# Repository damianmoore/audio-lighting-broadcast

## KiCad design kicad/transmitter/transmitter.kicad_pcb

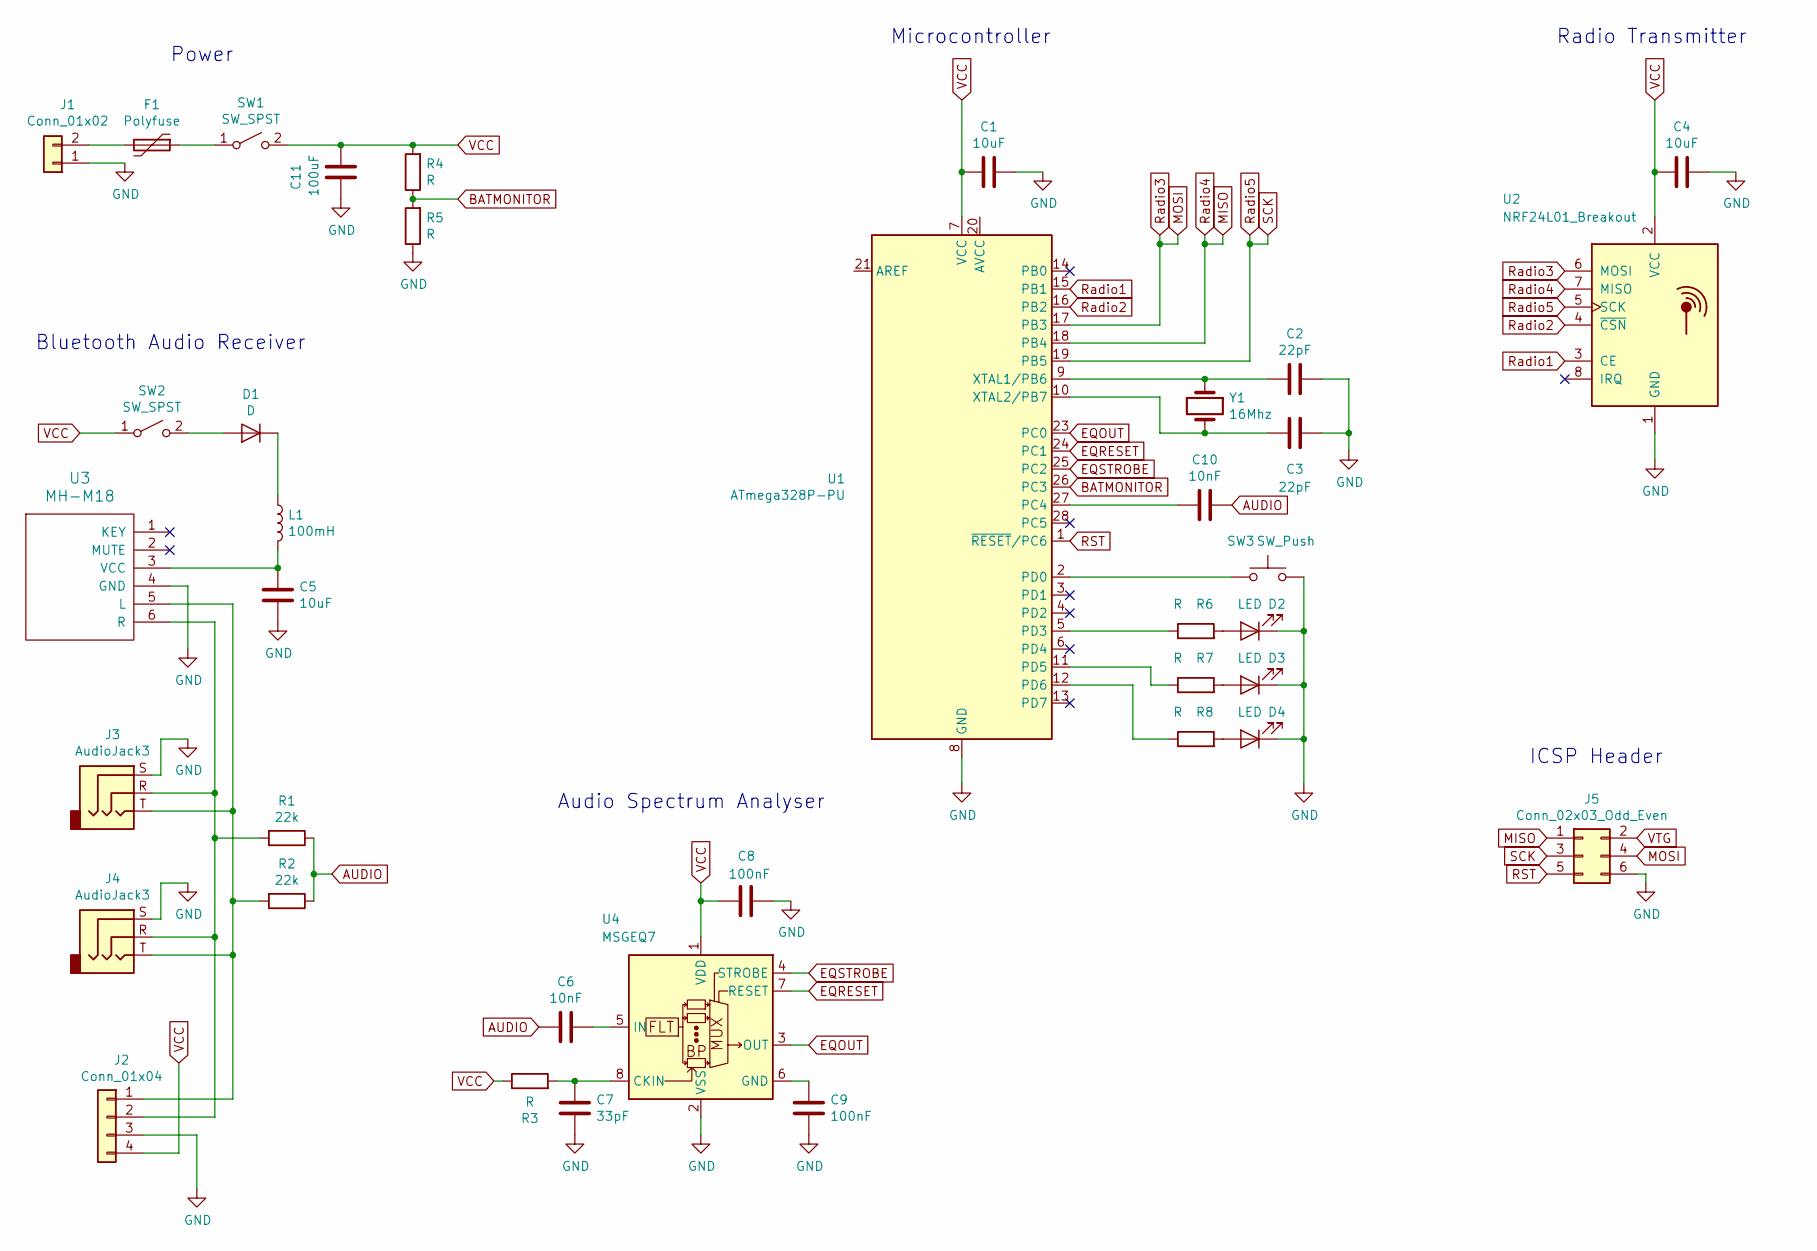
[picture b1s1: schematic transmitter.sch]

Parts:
C1, C4, C5: 10uF; C_0603_1608Metric_Pad1.05x0.95mm_HandSolder
C2, C3: 22pF; C_0603_1608Metric_Pad1.05x0.95mm_HandSolder
C6, C10: 10nF; C_0603_1608Metric_Pad1.05x0.95mm_HandSolder
C7: 33pF; C_0603_1608Metric_Pad1.05x0.95mm_HandSolder
C8, C9: 100nF; C_0603_1608Metric_Pad1.05x0.95mm_HandSolder
C11: 100uF; CP_Radial_D6.3mm_P2.50mm
D1: D; D_A-405_P7.62mm_Horizontal
D2, D3, D4: LED; LED_D3.0mm
F1: Polyfuse; Resonator-2Pin_W6.0mm_H3.0mm
J1: Conn_01x02; SolderWirePad_1x02_P3.81mm_Drill1mm
J2: Conn_01x04; PinHeader_1x04_P2.54mm_Vertical
J3, J4: AudioJack3; 3.5mm_Stereo_Jack
J5: Conn_02x03_Odd_Even; PinHeader_2x03_P2.54mm_Vertical
L1: 100mH; L_Toroid_Vertical_L16.0mm_W8.0mm_P7.62mm
R1, R2: 22k; R_0603_1608Metric_Pad1.05x0.95mm_HandSolder
R3, R4, R5, R6, R7, R8: R; R_0603_1608Metric_Pad1.05x0.95mm_HandSolder
SW1, SW2: SW_SPST; PinHeader_1x02_P2.54mm_Vertical
SW3: SW_Push; PinHeader_1x02_P2.54mm_Vertical
U1: ATmega328P-PU; DIP-28_W7.62mm
U2: NRF24L01_Breakout; nRF24L01_Breakout
U3: MH-M18; MH-M18_Bluetooth_Audio
U4: MSGEQ7; DIP-8_W10.16mm
Y1: 16Mhz; Crystal_HC18-U_Vertical

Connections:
AUDIO: C6.2, C10.1, R1.1, R2.1
BATMONITOR: R4.1, R5.2, U1.26 (PC3)
EQOUT: U1.23 (PC0), U4.3 (OUT)
EQRESET: U1.24 (PC1), U4.7 (RESET)
EQSTROBE: U1.25 (PC2), U4.4 (STROBE)
GND: C1.1, C2.1, C3.1, C4.1, C5.2, C7.1, C8.2, C9.1, C11.1, D2.1 (K), D3.1 (K), D4.1 (K), J1.1, J2.3, J3.S, J4.S, J5.6, R5.1, SW3.2, U1.8 (GND), U1.22 (GND), U2.1 (GND), U3.4 (GND), U4.2 (VSS)
MISO: J5.1, U1.18 (PB4), U2.7 (MISO)
MOSI: J5.4, U1.17 (PB3), U2.6 (MOSI)
unnamed: C2.2, U1.9 (XTAL1/PB6), Y1.1
unnamed: C3.2, U1.10 (XTAL2/PB7), Y1.2
unnamed: C5.1, L1.2, U3.3 (VCC)
unnamed: C6.1, U4.5 (IN)
unnamed: C7.2, R3.2, U4.8 (CKIN)
unnamed: C9.2, U4.6 (GND)
unnamed: C10.2, U1.27 (PC4)
unnamed: D1.1 (K), L1.1
unnamed: D1.2 (A), SW2.2 (B)
unnamed: D2.2 (A), R6.2
unnamed: D3.2 (A), R7.2
unnamed: D4.2 (A), R8.2
unnamed: F1.1, SW1.1 (A)
unnamed: F1.2, J1.2
unnamed: J2.1, J3.T, J4.T, R2.2, U3.5 (L)
unnamed: J2.2, J3.R, J4.R, R1.2, U3.6 (R)
unnamed: R6.1, U1.5 (PD3)
unnamed: R7.1, U1.11 (PD5)
unnamed: R8.1, U1.12 (PD6)
unnamed: SW3.1, U1.2 (PD0)
RST: J5.5, U1.1 (~RESET~/PC6)
Radio1: U1.15 (PB1), U2.3 (CE)
Radio2: U1.16 (PB2), U2.4 (~CSN)
Radio5: J5.3, U1.19 (PB5), U2.5 (SCK)
VCC: C1.2, C4.2, C8.1, C11.2, J2.4, R3.1, R4.2, SW1.2 (B), SW2.1 (A), U1.7 (VCC), U2.2 (VCC), U4.1 (VDD)
VTG: J5.2

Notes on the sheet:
Power
Bluetooth Audio Receiver
Audio Spectrum Analyser
Microcontroller
Radio Transmitter
ICSP Header

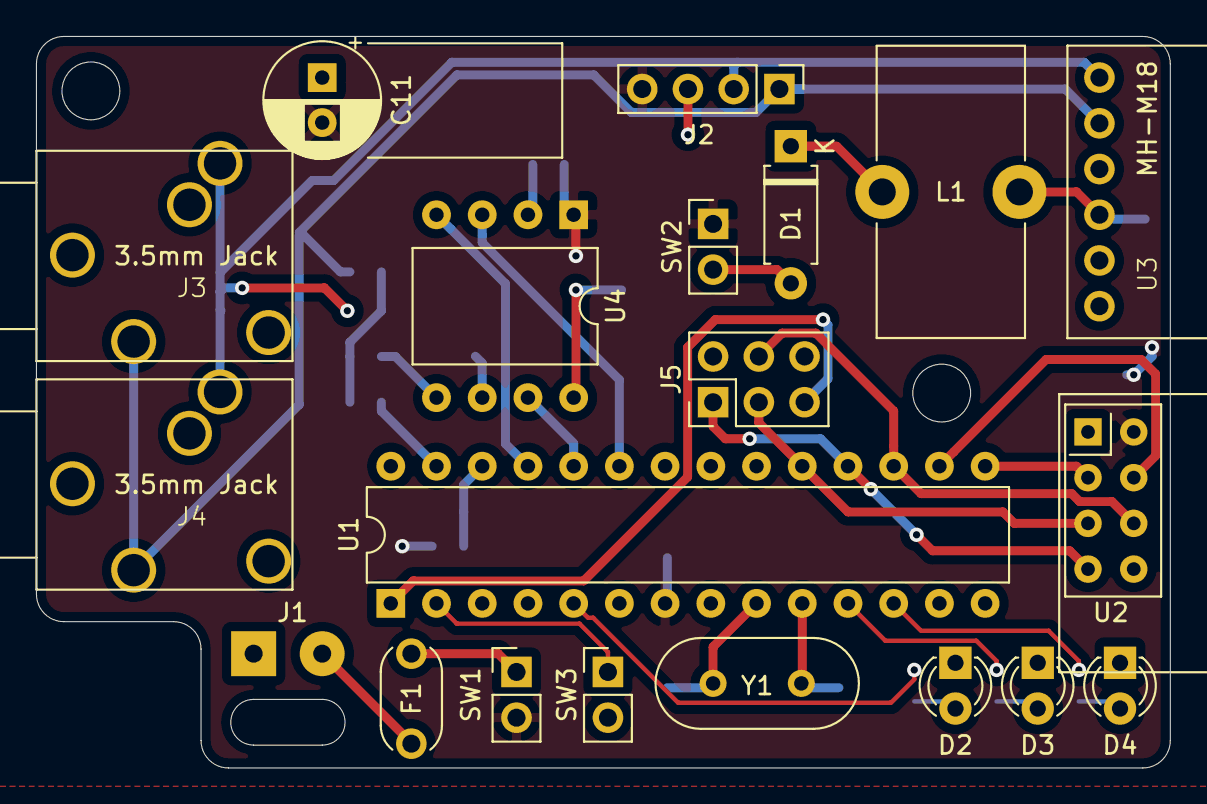
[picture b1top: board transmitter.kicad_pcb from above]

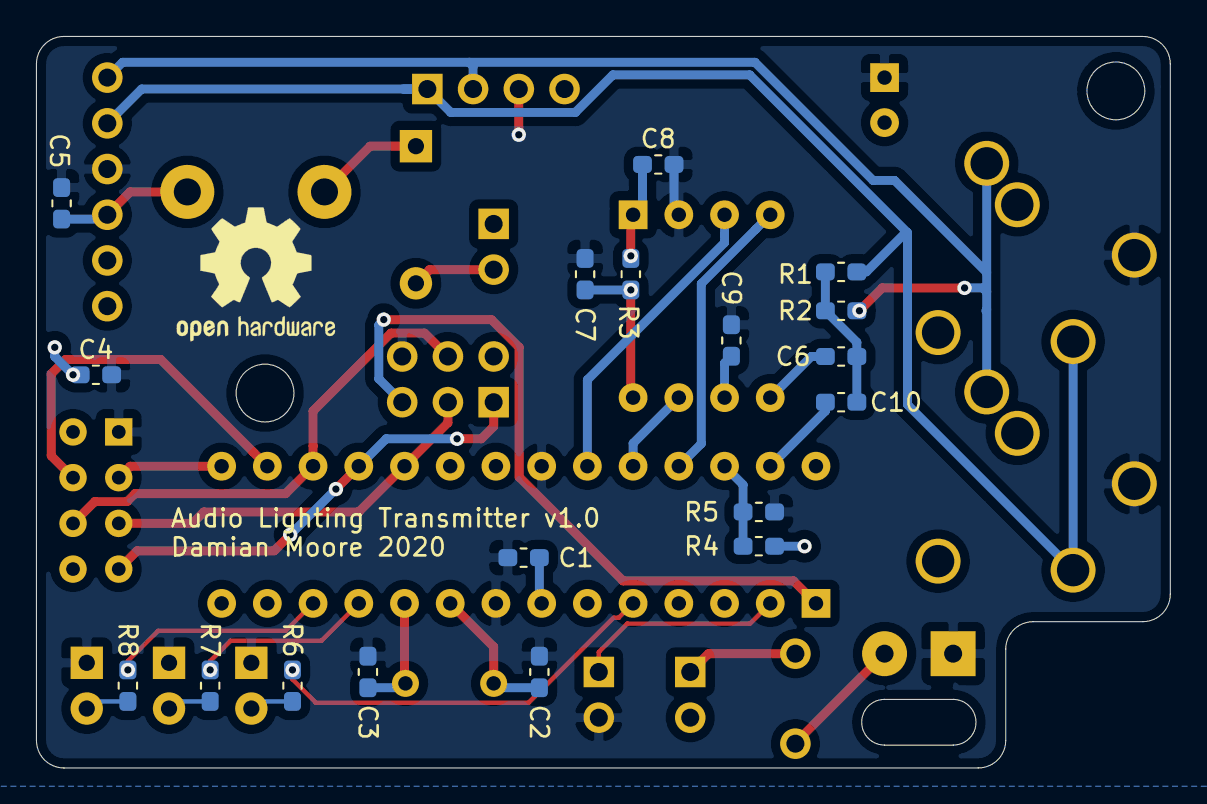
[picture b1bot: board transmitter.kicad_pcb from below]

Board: 2 copper layers, 63.0 x 40.6 mm, 38 parts (18 on the bottom side), 33 nets.

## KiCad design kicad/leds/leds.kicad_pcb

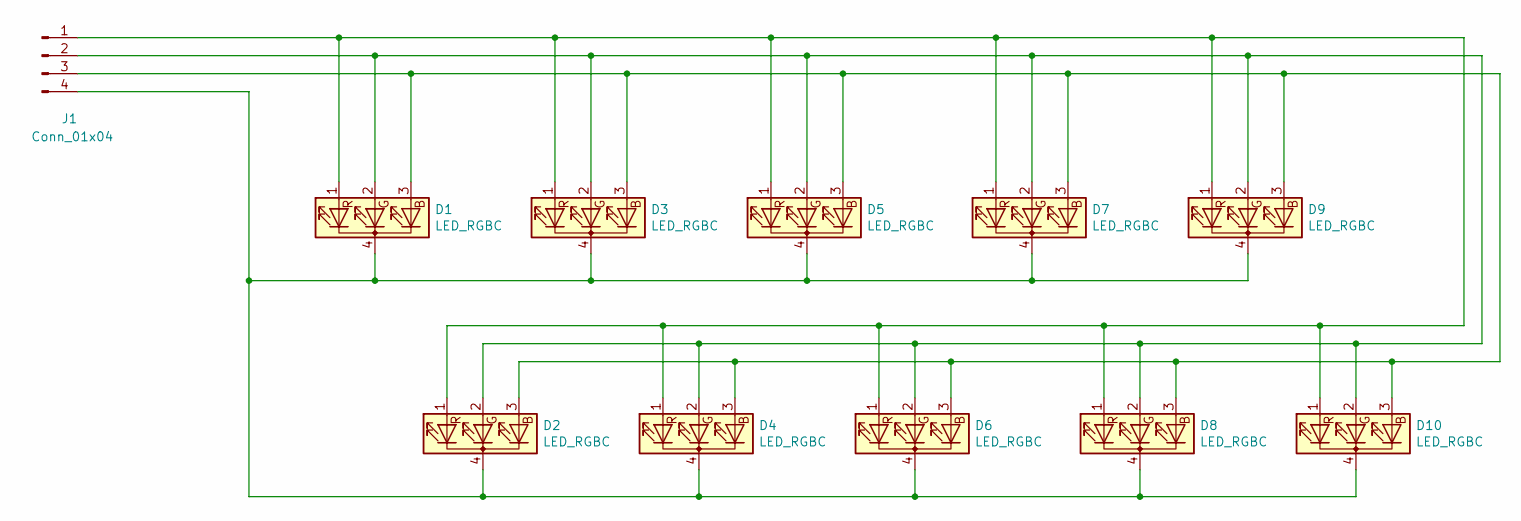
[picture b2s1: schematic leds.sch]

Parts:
D1, D2, D3, D4, D5, D6, D7, D8, D9, D10: LED_RGBC; LED_D5.0mm-4_RGB_swapped_pins
J1: Conn_01x04; Pin_Header_Straight_Simplified_1x04_Pitch2.54mm

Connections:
unnamed: D1.1 (RA), D2.1 (RA), D3.1 (RA), D4.1 (RA), D5.1 (RA), D6.1 (RA), D7.1 (RA), D8.1 (RA), D9.1 (RA), D10.1 (RA), J1.1
unnamed: D1.2 (GA), D2.2 (GA), D3.2 (GA), D4.2 (GA), D5.2 (GA), D6.2 (GA), D7.2 (GA), D8.2 (GA), D9.2 (GA), D10.2 (GA), J1.2
unnamed: D1.3 (BA), D2.3 (BA), D3.3 (BA), D4.3 (BA), D5.3 (BA), D6.3 (BA), D7.3 (BA), D8.3 (BA), D9.3 (BA), D10.3 (BA), J1.3
unnamed: D1.4 (K), D2.4 (K), D3.4 (K), D4.4 (K), D5.4 (K), D6.4 (K), D7.4 (K), D8.4 (K), D9.4 (K), D10.4 (K), J1.4

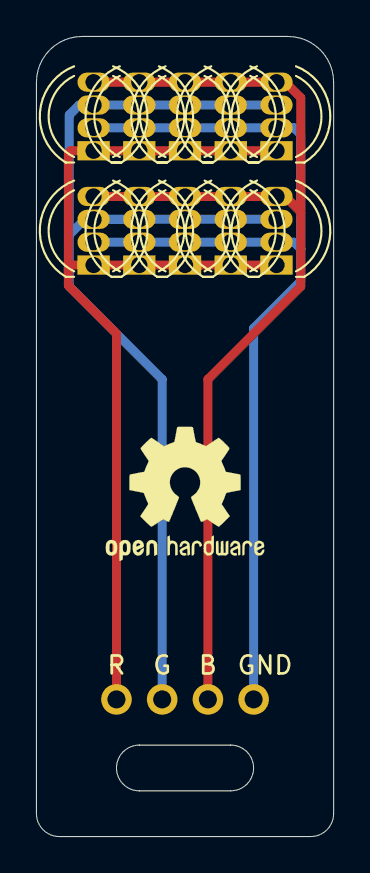
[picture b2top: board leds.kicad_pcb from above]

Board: 2 copper layers, 16.5 x 44.5 mm, 11 parts (0 on the bottom side), 4 nets.

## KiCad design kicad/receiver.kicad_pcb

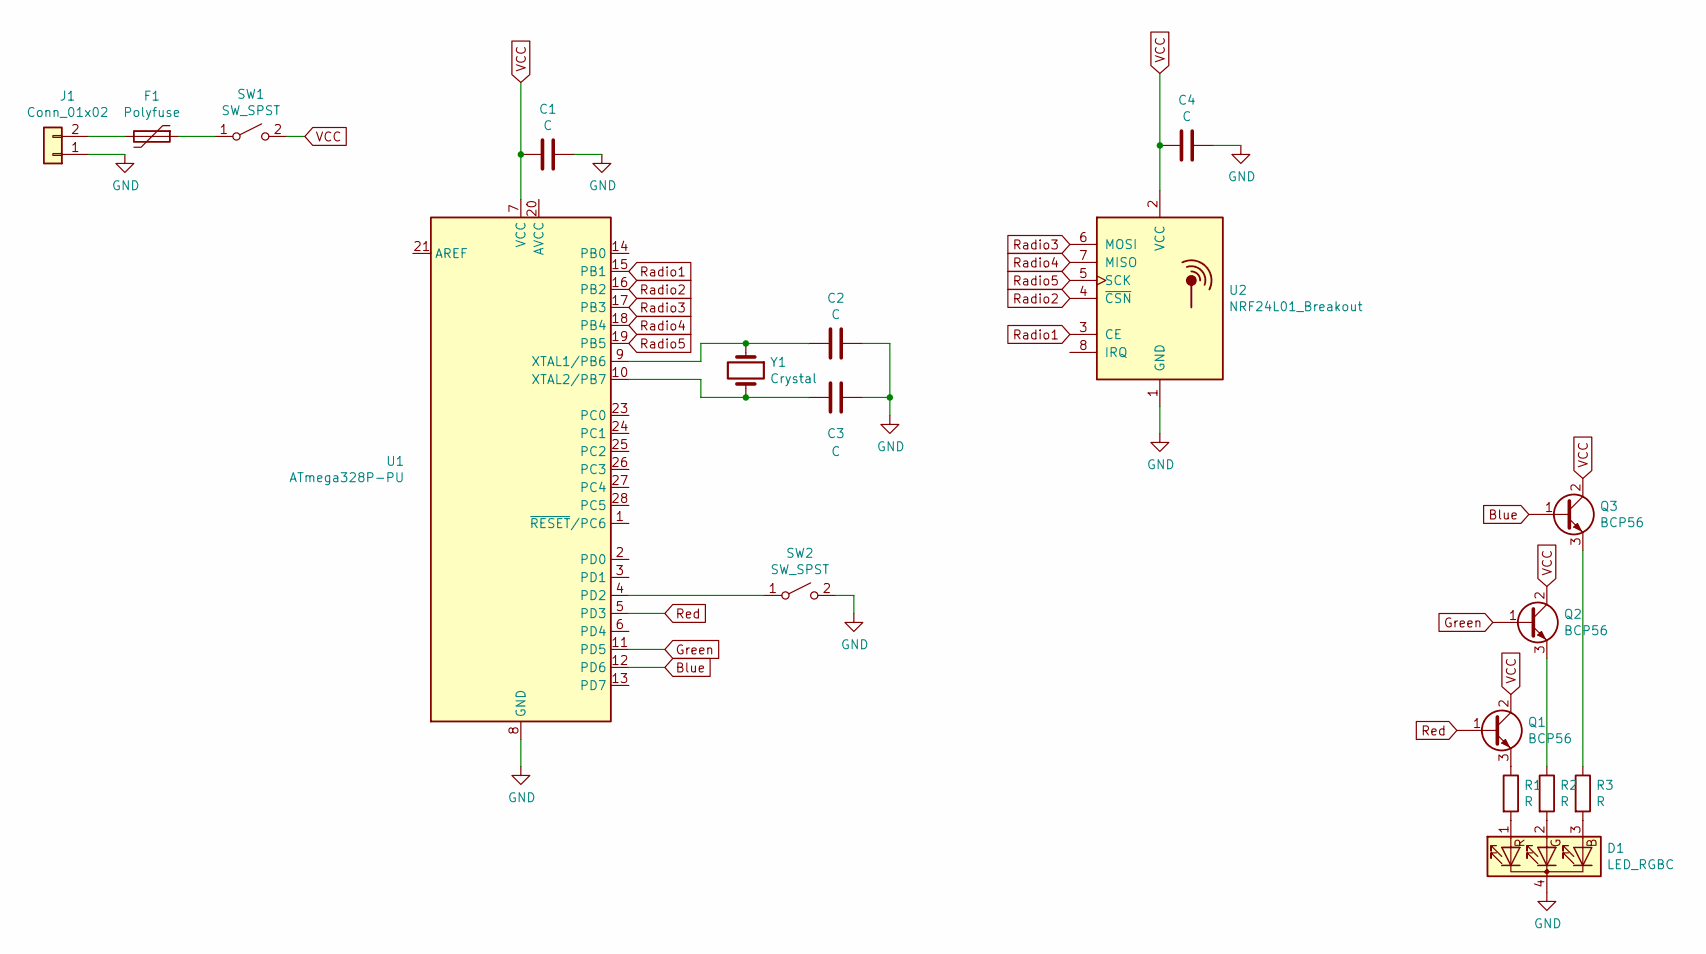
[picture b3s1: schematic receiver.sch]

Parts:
C1, C2, C3, C4: C; C_Disc_D3.0mm_W1.6mm_P2.50mm
D1: LED_RGBC; SolderWirePad_1x04_P3.175mm_Drill0.8mm
F1: Polyfuse; Crystal_HC18-U_Vertical
J1: Conn_01x02; SolderWirePad_1x02_P3.81mm_Drill1mm
Q1, Q2, Q3: BCP56; SOT-223-3_TabPin2
R1, R2, R3: R; R_Axial_DIN0207_L6.3mm_D2.5mm_P7.62mm_Horizontal
SW1, SW2: SW_SPST; SolderWirePad_1x02_P3.81mm_Drill1mm
U1: ATmega328P-PU; DIP-28_W7.62mm
U2: NRF24L01_Breakout; nRF24L01_Breakout
Y1: Crystal; Crystal_HC18-U_Vertical

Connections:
Blue: Q3.1 (B), U1.12 (PD6)
GND: C1.1, C2.1, C3.1, C4.1, D1.4 (K), J1.1, SW2.2 (B), U1.8 (GND), U1.22 (GND), U2.1 (GND)
Green: Q2.1 (B), U1.11 (PD5)
unnamed: C2.2, U1.9 (XTAL1/PB6), Y1.1
unnamed: C3.2, U1.10 (XTAL2/PB7), Y1.2
unnamed: D1.1 (RA), R1.2
unnamed: D1.2 (GA), R2.2
unnamed: D1.3 (BA), R3.2
unnamed: F1.1, SW1.1 (A)
unnamed: F1.2, J1.2
unnamed: Q1.3 (E), R1.1
unnamed: Q2.3 (E), R2.1
unnamed: Q3.3 (E), R3.1
unnamed: SW2.1 (A), U1.4 (PD2)
Radio1: U1.15 (PB1), U2.3 (CE)
Radio2: U1.16 (PB2), U2.4 (~CSN)
Radio3: U1.17 (PB3), U2.6 (MOSI)
Radio4: U1.18 (PB4), U2.7 (MISO)
Radio5: U1.19 (PB5), U2.5 (SCK)
Red: Q1.1 (B), U1.5 (PD3)
VCC: C1.2, C4.2, Q1.2 (C), Q1.4 (C), Q2.2 (C), Q2.4 (C), Q3.2 (C), Q3.4 (C), SW1.2 (B), U1.7 (VCC), U2.2 (VCC)

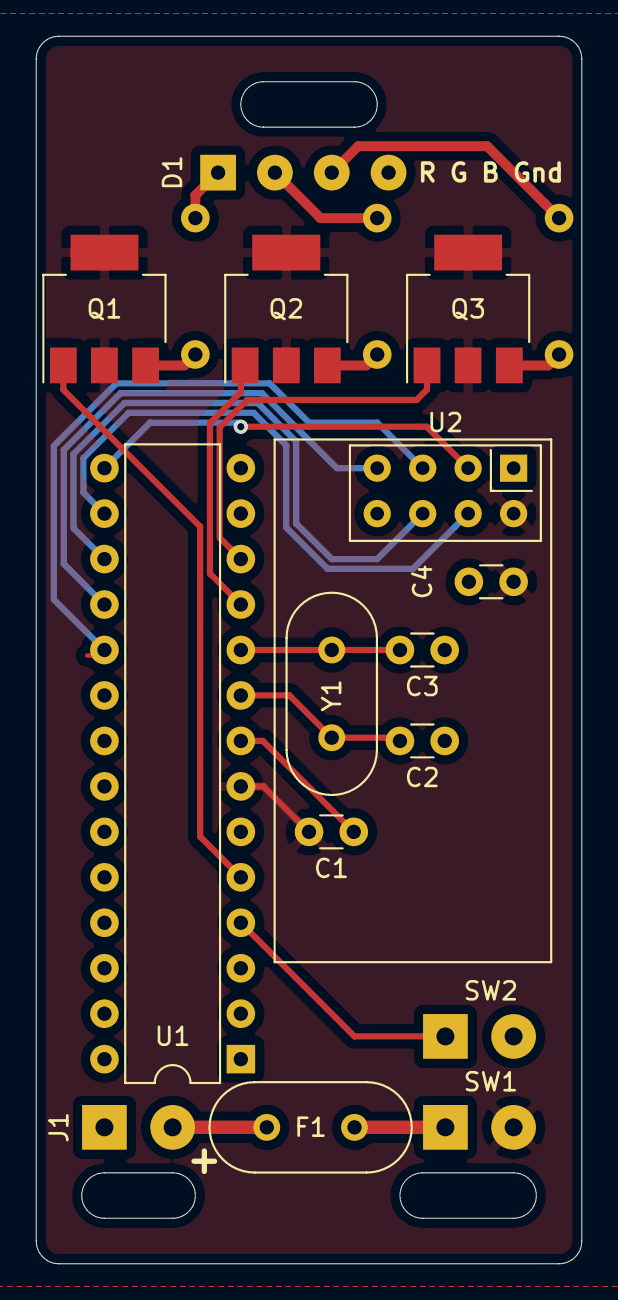
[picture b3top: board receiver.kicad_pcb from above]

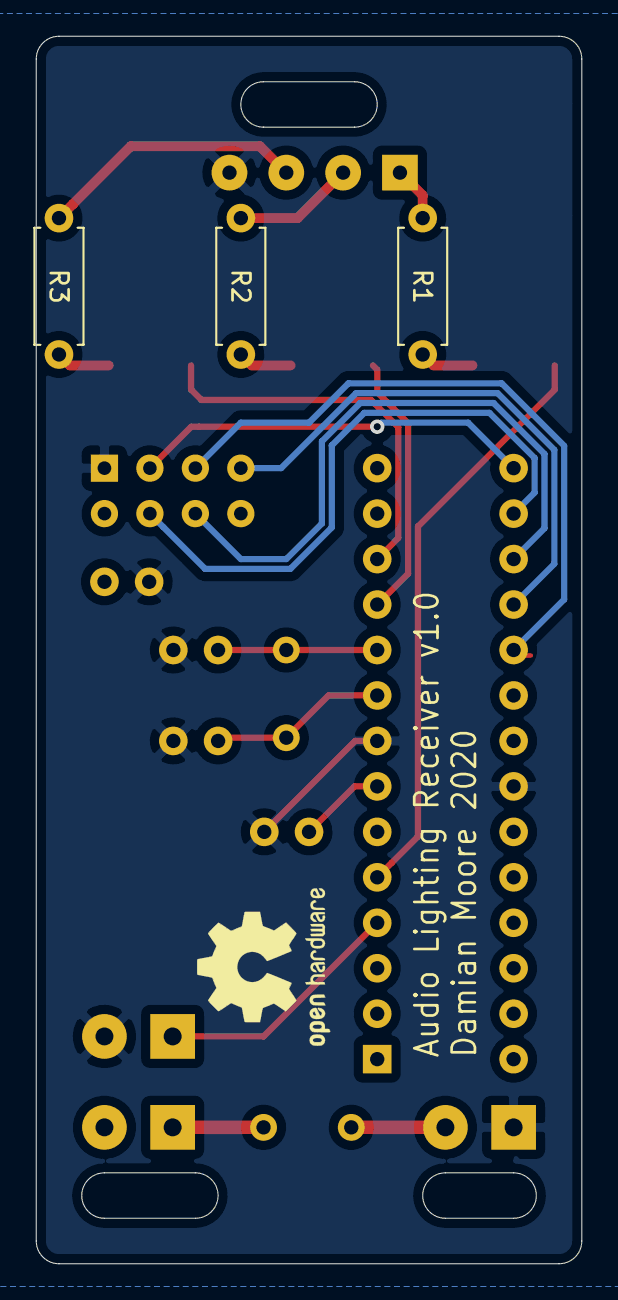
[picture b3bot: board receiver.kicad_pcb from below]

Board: 2 copper layers, 30.5 x 68.6 mm, 18 parts (3 on the bottom side), 21 nets.

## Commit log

2020-01-12 KiCad files for receiver
2020-01-12 Transmitter and receiver Arduino source files
2020-01-13 Receiver remembers which mode (bass/mid/treb) it was listening to across power-downs. Resets radio if a crash occurs.
2020-01-13 Increased responsiveness and data throughput. Scaling color intensity up based on historic maximum of each mode (bass/mid/treb).
2020-01-17 Refinements to bass/mid/treb flashes
2020-01-17 CNC Gcode files for case end caps
2020-02-06 Schematic and PCB for LEDs
2020-02-06 Tweaks to transmitter code
2020-02-11 Updates to transmitter code
2020-02-11 First pass at transmitter schematic and PCB
2020-02-11 Button, LEDs, ICSP header
2020-02-11 Tidy-ups pre-order
2020-02-24 Removes unused silkscreen symbol from PCB
2020-02-29 Code for colour controller
2020-03-12 Resistor and capacitor values
